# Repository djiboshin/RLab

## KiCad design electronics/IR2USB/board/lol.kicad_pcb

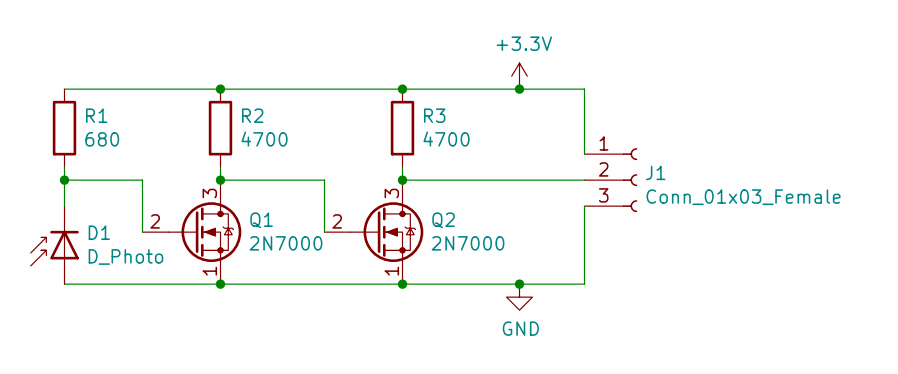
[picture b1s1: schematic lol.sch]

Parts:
D1: D_Photo; R_LDR_4.9x4.2mm_P2.54mm_Vertical
J1: Conn_01x03_Female; PinHeader_1x03_P2.54mm_Vertical
Q1, Q2: 2N7000; TO-92_Inline
R1: 680; R_Axial_DIN0411_L9.9mm_D3.6mm_P12.70mm_Horizontal
R2, R3: 4700; R_Axial_DIN0411_L9.9mm_D3.6mm_P12.70mm_Horizontal

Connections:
+3V3: J1.1, R1.1, R2.1, R3.1
GND: D1.2 (A), J1.3, Q1.1 (S), Q2.1 (S)
unnamed: D1.1 (K), Q1.2 (G), R1.2
unnamed: J1.2, Q2.3 (D), R3.2
unnamed: Q1.3 (D), Q2.2 (G), R2.2

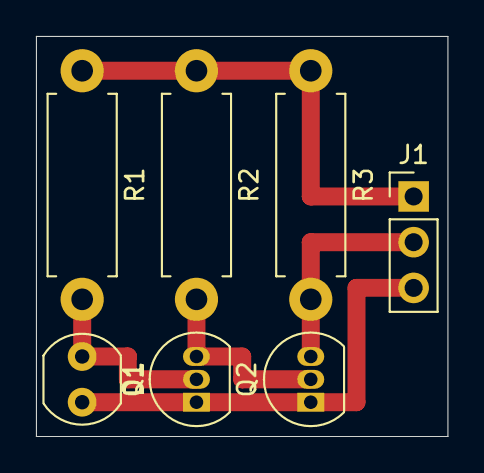
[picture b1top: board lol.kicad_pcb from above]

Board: 2 copper layers, 22.9 x 22.2 mm, 7 parts (0 on the bottom side), 5 nets.

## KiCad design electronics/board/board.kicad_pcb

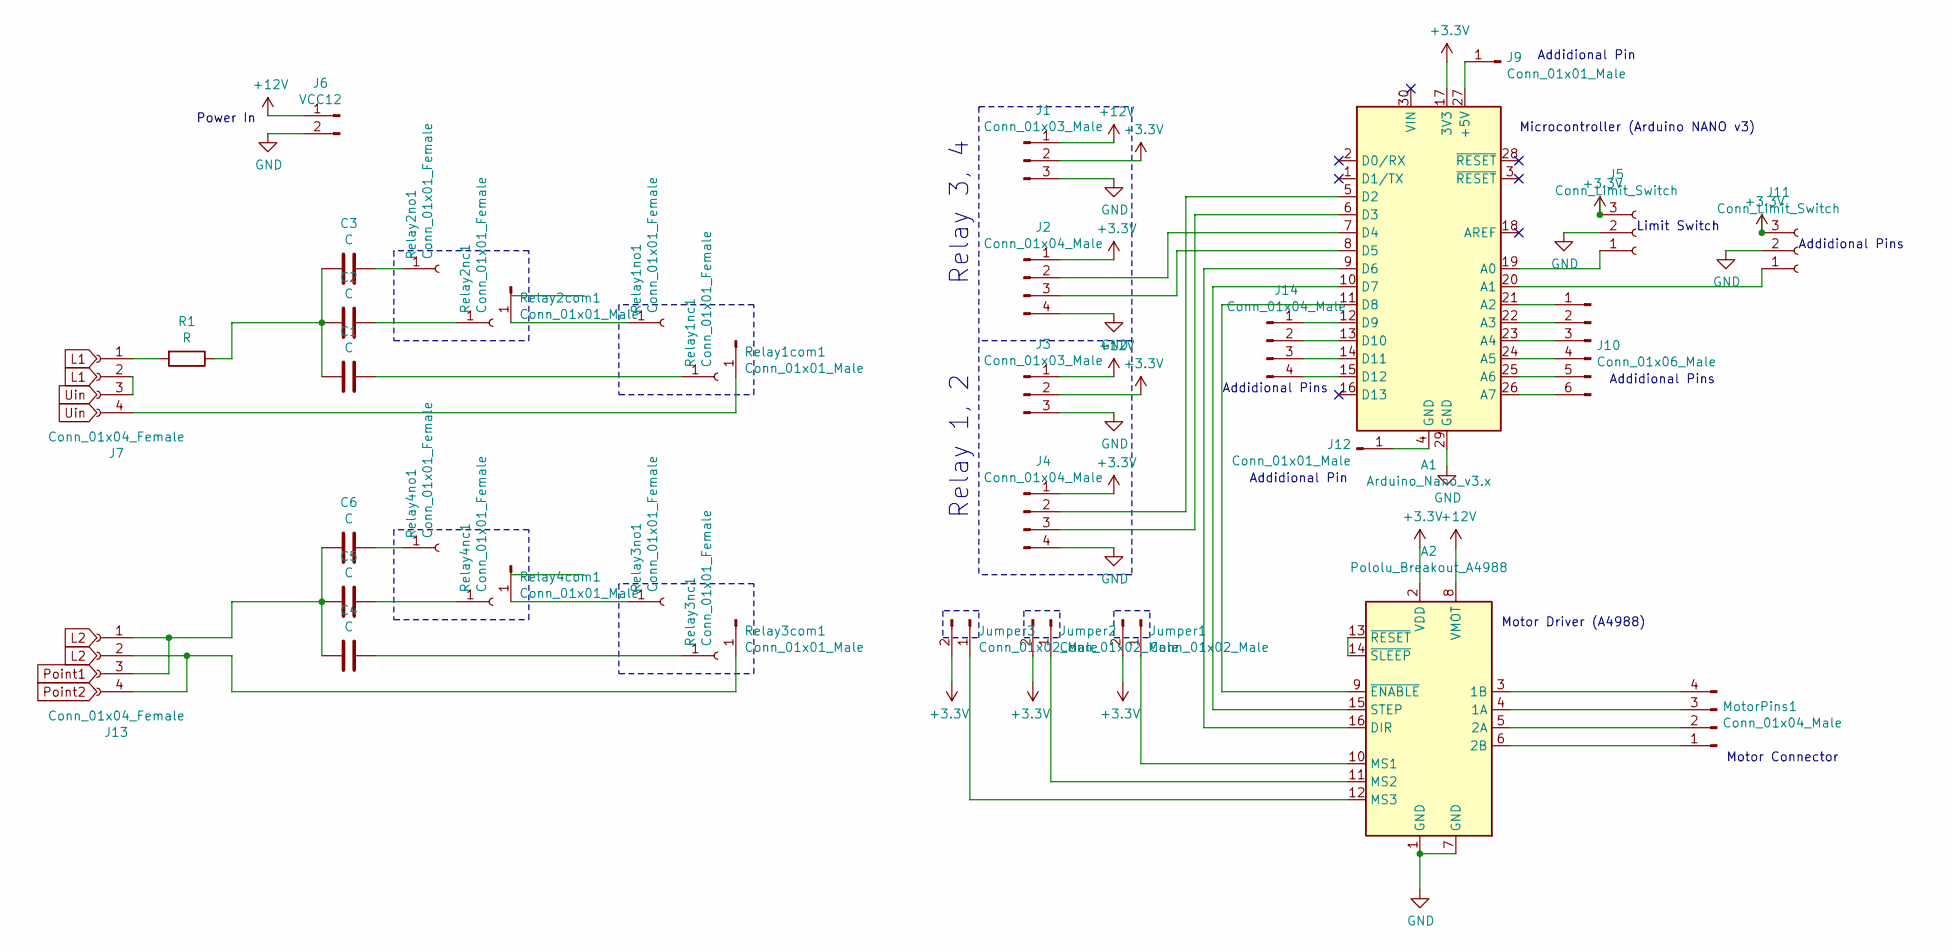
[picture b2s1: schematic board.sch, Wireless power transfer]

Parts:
A1: Arduino_Nano_v3.x; Arduino_Nano
A2: Pololu_Breakout_A4988; Pololu_Breakout-16_15.2x20.3mm
C1, C2, C3, C4, C5, C6: C; C_Disc_D5.0mm_W2.5mm_P5.00mm
J1, J3: Conn_01x03_Male; PinSocket_1x03_P2.54mm_Vertical
J2, J4: Conn_01x04_Male; PinSocket_1x04_P2.54mm_Vertical
J5, J11: Conn_Limit_Switch; PinHeader_1x03_P2.54mm_Vertical
J6: VCC12; TerminalBlock_Phoenix_MKDS-1,5-2-5.08_1x02_P5.08mm_Horizont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
J7, J13: Conn_01x04_Female; TerminalBlock_Phoenix_MKDS-1,5-4-5.08_1x04_P5.08mm_Horizont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
J9, J12: Conn_01x01_Male; PinHeader_1x01_P2.54mm_Vertical
J10: Conn_01x06_Male; PinHeader_1x06_P2.54mm_Vertical
J14: Conn_01x04_Male; PinHeader_1x04_P2.54mm_Vertical
Jumper1, Jumper2, Jumper3: Conn_01x02_Male; PinHeader_1x02_P2.54mm_Vertical
MotorPins1: Conn_01x04_Male; PinHeader_1x04_P2.54mm_Vertical
R1: R; R_Axial_DIN0207_L6.3mm_D2.5mm_P10.16mm_Horizontal
Relay1com1, Relay2com1, Relay3com1, Relay4com1: Conn_01x01_Male; SolderWire-1sqmm_1x01_D1.4mm_OD2.7mm
Relay1nc1, Relay1no1, Relay2nc1, Relay2no1, Relay3nc1, Relay3no1, Relay4nc1, Relay4no1: Conn_01x01_Female; SolderWire-1sqmm_1x01_D1.4mm_OD2.7mm

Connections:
+3V3: A1.17 (3V3), A2.2 (VDD), J1.2, J2.1, J3.2, J4.1, J5.3, J11.3, Jumper1.2, Jumper2.2, Jumper3.2
+12V: A2.8 (VMOT), J1.1, J3.1, J6.1
GND: A1.29 (GND), A2.1 (GND), A2.7 (GND), J1.3, J2.4, J3.3, J4.4, J5.2, J6.2, J11.2
unnamed: A1.4 (GND), J12.1
unnamed: A1.5 (D2), J4.2
unnamed: A1.6 (D3), J4.3
unnamed: A1.7 (D4), J2.2
unnamed: A1.8 (D5), J2.3
unnamed: A1.9 (D6), A2.16 (DIR)
unnamed: A1.10 (D7), A2.15 (STEP)
unnamed: A1.11 (D8), A2.9 (~ENABLE)
unnamed: A1.12 (D9), J14.1
unnamed: A1.13 (D10), J14.2
unnamed: A1.14 (D11), J14.3
unnamed: A1.15 (D12), J14.4
unnamed: A1.19 (A0), J5.1
unnamed: A1.20 (A1), J11.1
unnamed: A1.21 (A2), J10.1
unnamed: A1.22 (A3), J10.2
unnamed: A1.23 (A4), J10.3
unnamed: A1.24 (A5), J10.4
unnamed: A1.25 (A6), J10.5
unnamed: A1.26 (A7), J10.6
unnamed: A1.27 (+5V), J9.1
unnamed: A2.3 (1B), MotorPins1.4
unnamed: A2.4 (1A), MotorPins1.3
unnamed: A2.5 (2A), MotorPins1.2
unnamed: A2.6 (2B), MotorPins1.1
unnamed: A2.10 (MS1), Jumper1.1
unnamed: A2.11 (MS2), Jumper2.1
unnamed: A2.12 (MS3), Jumper3.1
unnamed: A2.13 (~RESET), A2.14 (~SLEEP)
unnamed: C1.1, C2.1, C3.1, R1.1
unnamed: C1.2, Relay1nc1.1
unnamed: C2.2, Relay2nc1.1
unnamed: C3.2, Relay2no1.1
unnamed: C4.1, C5.1, C6.1, J13.1, J13.3
unnamed: C4.2, Relay3nc1.1
unnamed: C5.2, Relay4nc1.1
unnamed: C6.2, Relay4no1.1
unnamed: J7.1, R1.2
unnamed: J7.2, J7.3
unnamed: J7.4, Relay1com1.1
unnamed: J13.2, J13.4, Relay3com1.1
unnamed: Relay1no1.1, Relay2com1.1
unnamed: Relay3no1.1, Relay4com1.1

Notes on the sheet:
Relay 3, 4
Relay 1, 2
Power In
Limit Switch
Motor Connector
Motor Driver (A4988)
Microcontroller (Arduino NANO v3)
Addidional Pins
Addidional Pin

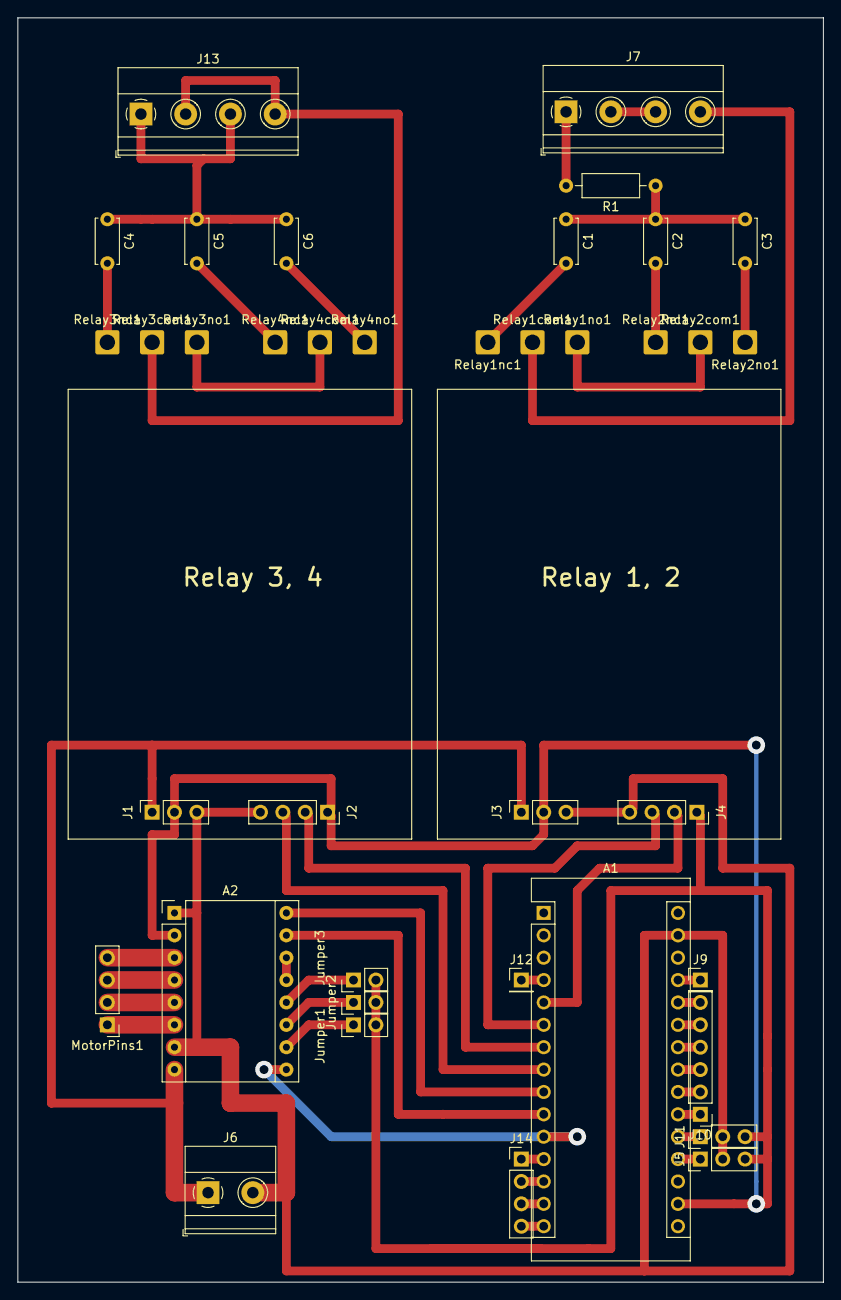
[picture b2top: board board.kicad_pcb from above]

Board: 2 copper layers, 91.4 x 143.5 mm, 38 parts (0 on the bottom side), 46 nets.

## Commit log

2022-03-15 Create LICENSE
